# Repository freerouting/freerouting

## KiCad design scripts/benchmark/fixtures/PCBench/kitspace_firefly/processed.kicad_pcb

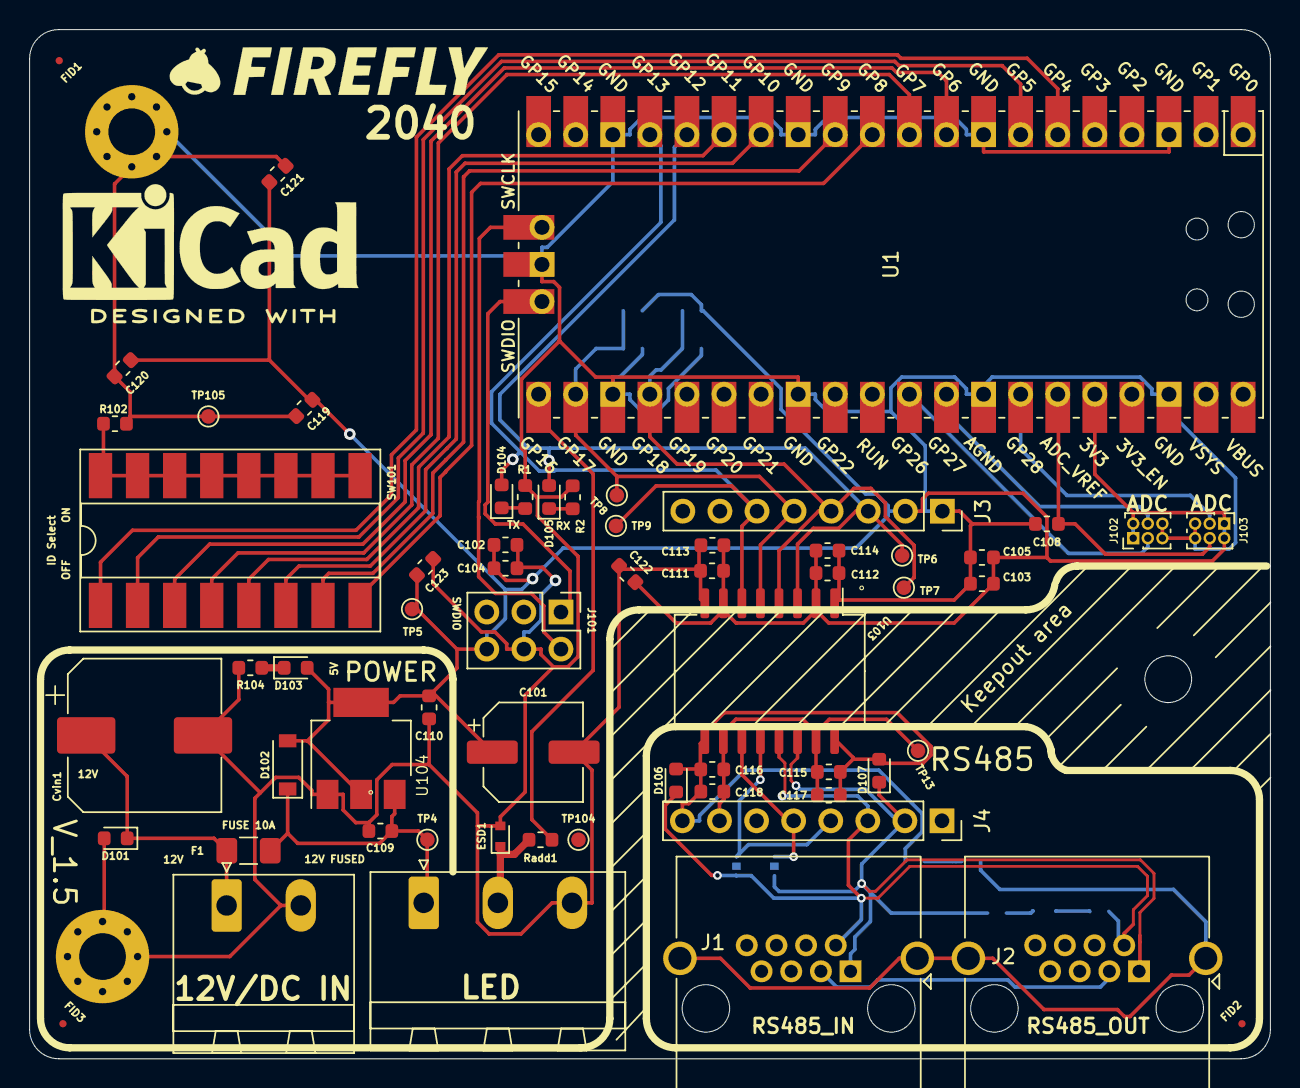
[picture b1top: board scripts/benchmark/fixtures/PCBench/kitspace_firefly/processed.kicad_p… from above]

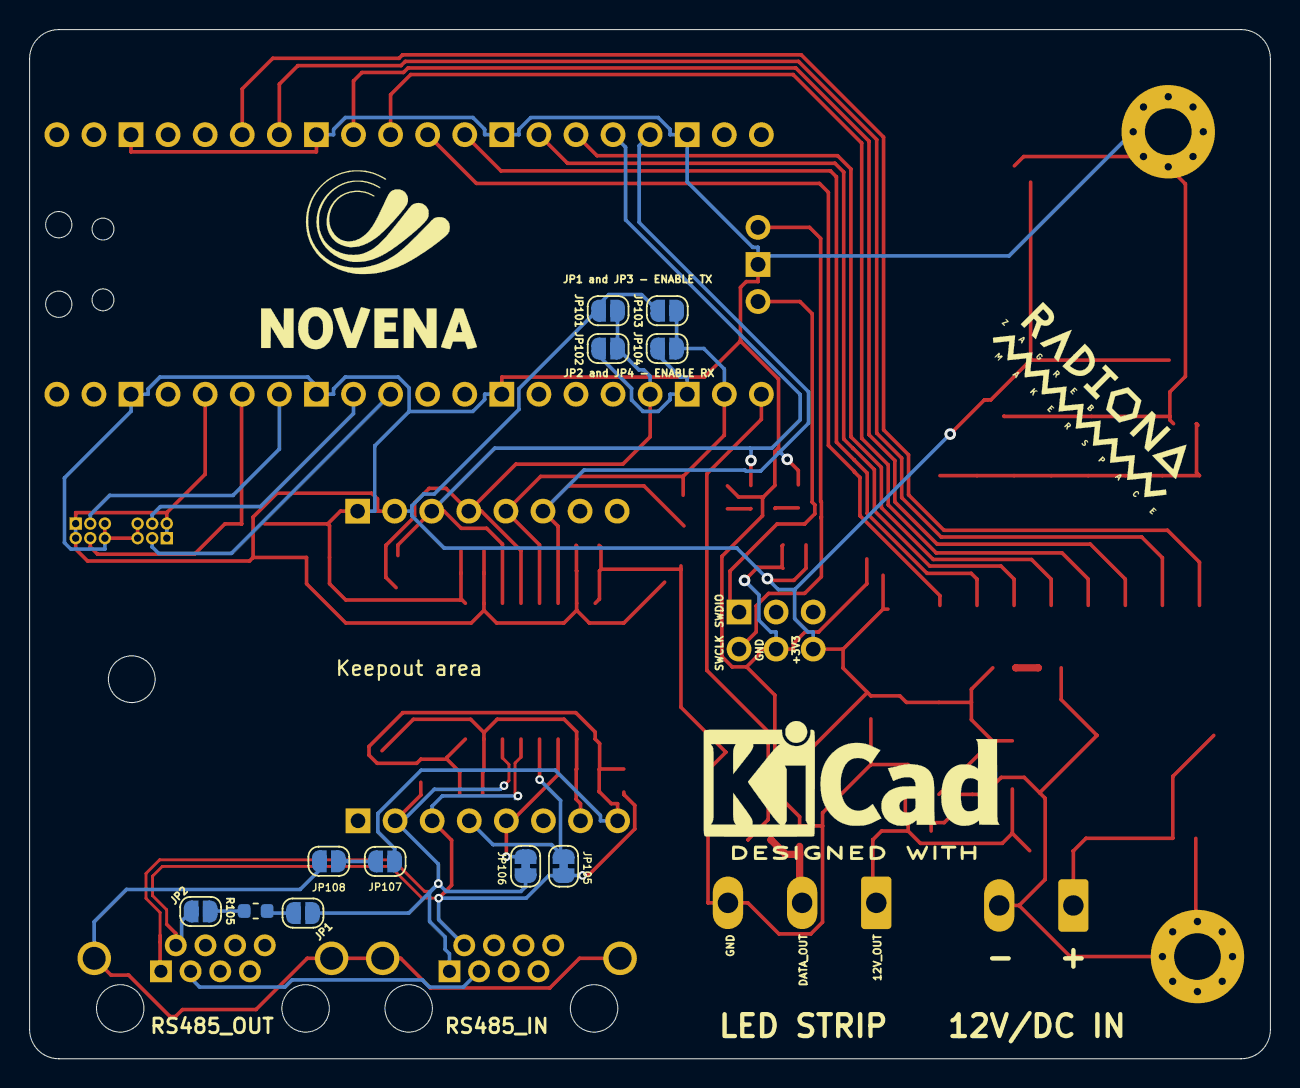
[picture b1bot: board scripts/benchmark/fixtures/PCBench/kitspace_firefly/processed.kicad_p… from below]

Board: 4 copper layers, 85.0 x 70.5 mm, 75 parts (11 on the bottom side), 39 nets.

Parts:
C101: 100uF/16V; CP_Elec_6.3x5.3
C102, C103, C108, C113, C114, C117, C118, C119, C120, C121, C122, C123: 100n; C_0603_1608Metric
C104, C105, C111, C112, C115, C116: 10n; C_0603_1608Metric
C109, C110: 1uF; C_0603_1608Metric
Cvin1: 100µF 50V 27mΩ; CP_Elec_10x10
D101, D106, D107: 82306120029; D_0603_1608Metric
D102: D_Schottky_Small; D_SOD-123
D103: LED_3V; LED_0603_1608Metric
D104, D105: LED_5V; LED_0603_1608Metric
ESD1: PESD5V0X1UAB; D_SOD-523
F1: Fuse DNP; Fuse_1206_3216Metric_Pad1.42x1.75mm_HandSolder
FID1: FID_ATM; Fiducial_0.5mm_Mask1mm
FID2: FID_GUL; Fiducial_0.5mm_Mask1mm
FID3: FID_TLV; Fiducial_0.5mm_Mask1mm
H1, H2: MountingHole; MountingHole_3.2mm_M3_Pad_Via
H3: MountingHole; MountingHole_3.2mm_M3
J1, J2: RJ45_Shielded; RJ45_Amphenol_RJHSE5380
J3, J4: Conn_01x08; PinSocket_1x08_P2.54mm_Vertical
J101: Conn_02x03_Counter_Clockwise; PinHeader_2x03_P2.54mm_Vertical
J102: Analog_1_2; PinHeader_2x03_P1.00mm_Vertical
J103: Analog_3_4; PinHeader_2x03_P1.00mm_Vertical
JP1: ET1; SolderJumper-2_P1.3mm_Open_RoundedPad1.0x1.5mm
JP2: ET2; SolderJumper-2_P1.3mm_Open_RoundedPad1.0x1.5mm
JP101: Receiver_Disable1; SolderJumper-2_P1.3mm_Open_RoundedPad1.0x1.5mm
JP102: Receiver_Enable1; SolderJumper-2_P1.3mm_Open_RoundedPad1.0x1.5mm
JP103: Driver_Enable1; SolderJumper-2_P1.3mm_Open_RoundedPad1.0x1.5mm
JP104: Driver_Disable1; SolderJumper-2_P1.3mm_Open_RoundedPad1.0x1.5mm
JP105, JP106: SolderJumper_2_Open; SolderJumper-2_P1.3mm_Bridged_RoundedPad1.0x1.5mm
JP107, JP108: SolderJumper_2_Open; SolderJumper-2_P1.3mm_Open_RoundedPad1.0x1.5mm
Jadd1: MSTBA3; PhoenixContact_MSTBA_2,5_3-G-5,08_1x03_P5.08mm_Horizontal
Jc1: MSTBA2; PhoenixContact_MSTBA_2,5_2-G-5,08_1x02_P5.08mm_Horizontal
R1, R2, R104: 300; R_0603_1608Metric
R102: 1K; R_0603_1608Metric
R105: 120R; R_0603_1608Metric
Radd1: 1k; R_0603_1608Metric
SW101: SW_DIP_x08; DIP-16_W8.89mm_SMDSocket_LongPads
TP4: TP_Vin; TestPoint_Pad_D1.0mm
TP5: TP_3V3; TestPoint_Pad_D1.0mm
TP6: DMX_RX; TestPoint_Pad_D1.0mm
TP7: DMX_RE; TestPoint_Pad_D1.0mm
TP8: DMX_DE; TestPoint_Pad_D1.0mm
TP9: DMX_TX; TestPoint_Pad_D1.0mm
TP13: DMX_3V3; TestPoint_Pad_D1.0mm
TP104: TP_A; TestPoint_Pad_D1.0mm
TP105: TP_GND1; TestPoint_Pad_D1.0mm
U1: Pico; RPi_Pico_SMD_TH
U103: ADM2687E; SOIC-16W_7.5x12.8mm_P1.27mm
U104: AMS1117; SOT-223-3_TabPin2

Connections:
+3V3: C101.1, C102.1, C103.1, C104.1, C105.1, C110.1, C111.1, C112.2, C113.2, C114.1, C119.1, C120.1, C121.1, C122.1, C123.1, D102.2, D103.2, J3.2, J101.6, J102.1, J102.2, J103.1, J103.2, JP101.1, JP103.1, TP5.1, U1.36, U103.2, U103.7, U104.2
/A0: J102.3, U1.31
/A3: J102.4, U1.32
/A4: J103.3, U1.34
/A5: C108.1, J103.4, U1.35
/Addressable: Radd1.2, U1.21
/DMX_Enable_Receive: J3.4, JP101.2, JP102.1, TP7.1, U1.24, U103.4
/DMX_Enable_Send: J3.5, JP103.2, JP104.1, TP8.1, U1.22, U103.5
/DMX_Receive: D105.2, J3.3, TP6.1, U1.16, U103.3
/DMX_Send: D104.2, J3.6, TP9.1, U1.17, U103.6
/RS485_transciever/DMX+: D107.1, J1.1, J2.1, J4.2, JP1.1, JP106.2, U103.14
/RS485_transciever/DMX-: D106.1, J1.2, J2.2, J4.3, JP2.2, JP105.2, U103.13
/RS485_transciever/DMXTransmitterY: J4.5, JP106.1, U103.11
/RS485_transciever/DMXTransmitterZ: J4.4, JP105.1, U103.12
/RS485_transciever/DMXchassignd: J1.SH, J2.SH, JP108.2
/RS485_transciever/DMXgnd: JP107.2, JP108.1
/RS485_transciever/DXMgnd: J1.3, J2.3
/SWCLK: J101.2, U1.41
/SWDIO: J101.1, U1.43
/SW_1: SW101.1, U1.6
/SW_2: SW101.2, U1.7
/SW_3: SW101.3, U1.9
/SW_4: SW101.4, U1.10
/SW_5: SW101.5, U1.15
/SW_6: SW101.6, U1.14
/SW_7: SW101.7, U1.12
/SW_8: SW101.8, U1.11
/Vin: Cvin1.1, D101.1, F1.2, Jc1.1
DMX_3V: C115.1, C116.2, C117.1, C118.2, J4.7, TP13.1, U103.10, U103.15
GND1: C101.2, C102.2, C103.2, C104.2, C105.2, C108.2, C109.2, C110.2, C111.2, C112.1, C113.1, C114.2, C119.2, C120.2, C121.2, C122.2, C123.2, Cvin1.2, D101.2, ESD1.2, H1.1, H2.1, J3.1, J101.4, J102.5, J102.6, J103.5, J103.6, JP102.2, JP104.2, Jadd1.3, Jc1.2, R1.1, R2.1, R102.1, R104.1, TP105.1, U1.3, U1.8, U1.13, U1.18, U1.23, U1.28, U1.33, U1.38, U1.42, U103.1, U103.8, U104.1
GND2: C115.2, C116.1, C117.2, C118.1, D106.2, D107.2, J4.8, JP107.1, U103.9, U103.16
unnamed: D103.1, R104.2
unnamed: D104.1, R1.2
unnamed: D105.1, R2.2
unnamed: ESD1.1, Jadd1.2, Radd1.1
unnamed: JP1.2, R105.1
unnamed: JP2.1, R105.2
unnamed: R102.2, SW101.9, SW101.10, SW101.11, SW101.12, SW101.13, SW101.14, SW101.15, SW101.16
Vin_fused: C109.1, D102.1, F1.1, Jadd1.1, TP4.1, U104.3

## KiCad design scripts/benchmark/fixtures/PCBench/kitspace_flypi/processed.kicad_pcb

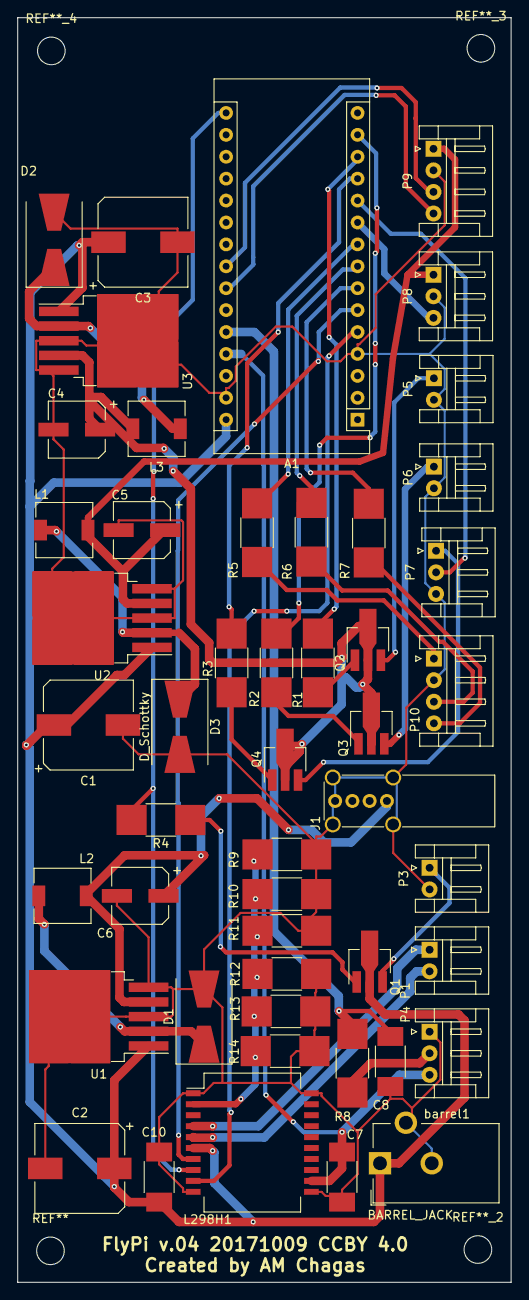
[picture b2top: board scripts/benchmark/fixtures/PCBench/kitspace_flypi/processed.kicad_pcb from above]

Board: 2 copper layers, 57.2 x 146.6 mm, 49 parts (0 on the bottom side), 38 nets.

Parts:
A1: Arduino_Nano_v3.x; Arduino_Nano
C1, C2, C3: 680µ; CP_Elec_10x10
C4, C5, C6: 220µ; CP_Elec_6.3x5.3
C7, C8, C10: 100n; C_1812_HandSoldering
D1, D2: Schottky 5A; D_SMB-SMC_Universal_Handsoldering
D3: D_Schottky; D_SMB-SMC_Universal_Handsoldering
J1: USB_A; USB_A_Vertical
L1, L2, L3: 33µH; L_6.3x6.3_H3
L298H1: L298P; HSOP-20-1EP_11.0x15.9mm_Pitch1.27mm_SlugUp
P1: PeltS1S2; JST_EH_S02B-EH_02x2.50mm_Angled
P3: Fan+-; JST_EH_S02B-EH_02x2.50mm_Angled
P4: Therm +s-; JST_EH_S03B-EH_03x2.50mm_Angled
P5: HP1+-; JST_EH_S02B-EH_02x2.50mm_Angled
P6: HP2+-; JST_EH_S02B-EH_02x2.50mm_Angled
P7: servo +s-; JST_EH_S03B-EH_03x2.50mm_Angled
P8: Ring +-s; JST_EH_S03B-EH_03x2.50mm_Angled
P9: matrix +-sdsc; JST_EH_S04B-EH_04x2.50mm_Angled
P10: RGB RG-B; JST_EH_S04B-EH_04x2.50mm_Angled
Q1, Q3, Q4: 1A_NPN_ECB; SOT-89-3_Handsoldering
Q2: 1A-NPN-ECB; SOT-89-3_Handsoldering
R1, R2, R3, R4: 270; R_1812_HandSoldering
R5, R6, R7: 220; R_1812_HandSoldering
R8: 1k1; R_1812_HandSoldering
R9, R10, R11, R12, R13, R14: 0.1m; R_1812_HandSoldering
U1, U2, U3: LM2596S-5; TO-263-5_TabPin3
barrel1: BARREL_JACK; Barrel_Jack_CUI_PJ-102AH

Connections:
GND: A1.4, A1.29, C1.2, C2.2, C3.2, C4.2, C5.2, C6.2, C7.2, C8.1, C10.1, D1.2, D2.2, D3.2, J1.4, J1.5, L298H1.1, L298H1.10, L298H1.11, L298H1.20, P3.2, P4.1, P5.2, P6.2, P7.3, P8.2, P9.2, P10.2, R9.1, R10.1, R11.1, R12.1, R13.1, R14.1, U1.3, U1.5, U2.3, U2.5, U3.3, U3.5, barrel1.2, barrel1.3
unnamed: A1.5, L298H1.9
unnamed: A1.6, L298H1.7
unnamed: A1.7, R7.2
unnamed: A1.8, R6.2
unnamed: A1.9, R5.2
unnamed: A1.10, P8.3
unnamed: A1.11, P7.2
unnamed: A1.12, R3.2
unnamed: A1.13, R1.2
unnamed: A1.14, R2.2
unnamed: A1.16, L298H1.8, R4.2
unnamed: A1.23, P9.3
unnamed: A1.24, P9.4
unnamed: A1.26, C8.2, R8.1
unnamed: A1.27, C7.1, L298H1.12, P4.3
unnamed: A1.30, C1.1, C2.1, C3.1, C10.2, L298H1.6, Q1.2, U1.1, U2.1, U3.1, barrel1.1
unnamed: C4.1, L3.2, Q2.2, Q3.2, Q4.2, U3.4
unnamed: C5.1, L1.2, P8.1, P9.1, U2.4
unnamed: C6.1, J1.1, L2.2, U1.4
unnamed: D1.1, L2.1, U1.2
unnamed: D2.1, L3.1, U3.2
unnamed: D3.1, L1.1, U2.2
unnamed: L298H1.2, R9.2, R10.2, R11.2, R12.2, R13.2, R14.2
unnamed: L298H1.4, P1.1
unnamed: L298H1.5, P1.2
unnamed: P3.1, Q1.3
unnamed: P4.2, R8.2
unnamed: P5.1, Q2.3
unnamed: P6.1, Q3.3
unnamed: P7.1, Q4.3
unnamed: P10.1, R5.1
unnamed: P10.3, R6.1
unnamed: P10.4, R7.1
unnamed: Q1.1, R4.1
unnamed: Q2.1, R1.1
unnamed: Q3.1, R2.1
unnamed: Q4.1, R3.1

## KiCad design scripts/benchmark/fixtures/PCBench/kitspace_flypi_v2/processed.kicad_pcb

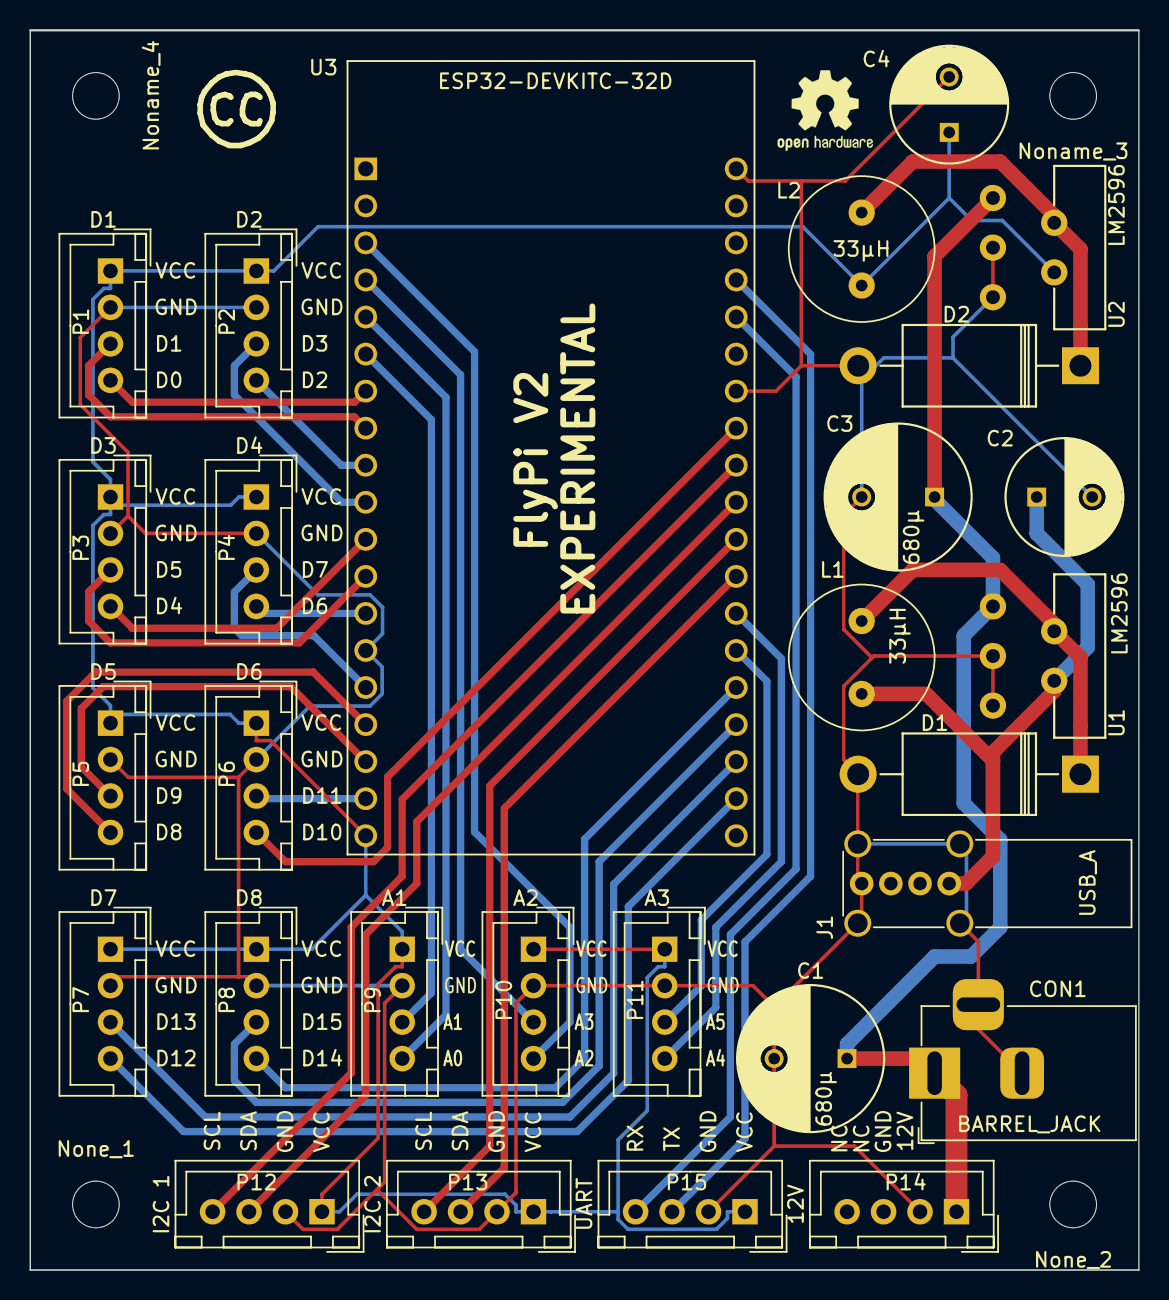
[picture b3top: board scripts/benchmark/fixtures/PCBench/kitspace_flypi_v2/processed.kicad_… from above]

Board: 2 copper layers, 76.0 x 85.0 mm, 35 parts (0 on the bottom side), 34 nets.

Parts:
C1, C3: 680µ; C_Radial_D10_L21_P5
C2, C4: 220µ; C_Radial_D8_L13_P3.8
CON1: BARREL_JACK; BarrelJack_Horizontal
D1, D2: Schottky 5A; Diode_DO-201AD_Horizontal_RM15
J1: USB_A; USB_A_Vertical
L1, L2: 33µH; Neosid_Inductor_MA-Bs75
Noname_1: Symbol_CreativeCommons_SilkScreenTop_Type2_Small
Noname_2: OSHW-Logo2_7.3x6mm_SilkScreen
Noname_3, Noname_4: MountingHole_3.2mm_M3_DIN965
Noname_5: (no value)
None_1, None_2: MountingHole_3.2mm_M3_DIN965
P1: D1; JST_XH_B04B-XH-A_04x2.50mm_Straight
P2: D2; JST_XH_B04B-XH-A_04x2.50mm_Straight
P3: D3; JST_XH_B04B-XH-A_04x2.50mm_Straight
P4: D4; JST_XH_B04B-XH-A_04x2.50mm_Straight
P5: D5; JST_XH_B04B-XH-A_04x2.50mm_Straight
P6: D6; JST_XH_B04B-XH-A_04x2.50mm_Straight
P7: D7; JST_XH_B04B-XH-A_04x2.50mm_Straight
P8: D8; JST_XH_B04B-XH-A_04x2.50mm_Straight
P9: A1; JST_XH_B04B-XH-A_04x2.50mm_Straight
P10: A2; JST_XH_B04B-XH-A_04x2.50mm_Straight
P11: A3; JST_XH_B04B-XH-A_04x2.50mm_Straight
P12: I2C 1; JST_XH_B04B-XH-A_04x2.50mm_Straight
P13: I2C 2; JST_XH_B04B-XH-A_04x2.50mm_Straight
P14: 12V; JST_XH_B04B-XH-A_04x2.50mm_Straight
P15: UART; JST_XH_B04B-XH-A_04x2.50mm_Straight
U1, U2: LM2596
U3: ESP32-DEVKITC-32D; MODULE_ESP32-DEVKITC-32D

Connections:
+5V: C4.1, L2.2, P1.1, P2.1, P3.1, P4.1, P5.1, P6.1, P7.1, P8.1, P9.1, P10.1, P11.1, P12.1, P13.1, P15.1, U2.4, U3.19
A1-3: P9.3, U3.6
A1-4: P9.4, U3.5
A2-3: P10.3, U3.4
A2-4: P10.4, U3.3
A3-3: P11.3, U3.33
A3-4: P11.4, U3.32
D1-3: P1.3, U3.8
D1-4: P1.4, U3.7
D2-3: P2.3, U3.10
D2-4: P2.4, U3.9
D3-3: P3.3, U3.12
D3-4: P3.4, U3.11
D4-3: P4.3, U3.15
D4-4: P4.4, U3.13
D5-3: P5.3, U3.17
D5-4: P5.4, U3.16
D6-3: P6.3, U3.18
D6-4: P6.4, U3.27
D7-3: P7.3, U3.36
D7-4: P7.4, U3.37
D8-3: P8.3, U3.35
D8-4: P8.4, U3.34
GND: C1.2, C2.2, C3.2, C4.2, CON1.2, CON1.3, D1.2, D2.2, J1.4, J1.5, P1.2, P2.2, P3.2, P4.2, P5.2, P6.2, P7.2, P8.2, P9.2, P10.2, P11.2, P12.2, P13.2, P14.2, P15.2, U1.3, U1.5, U2.3, U2.5, U3.14, U3.20, U3.26
I2C_1-3: P12.3, U3.29
I2C_1-4: P12.4, U3.28
I2C_2-3: P13.3, U3.31
I2C_2-4: P13.4, U3.30
unnamed: C1.1, C3.1, CON1.1, P14.1, U1.1, U2.1
unnamed: C2.1, J1.1, L1.2, U1.4
unnamed: D1.1, L1.1, U1.2
unnamed: D2.1, L2.1, U2.2
RX: P15.4, U3.24
TX: P15.3, U3.23
